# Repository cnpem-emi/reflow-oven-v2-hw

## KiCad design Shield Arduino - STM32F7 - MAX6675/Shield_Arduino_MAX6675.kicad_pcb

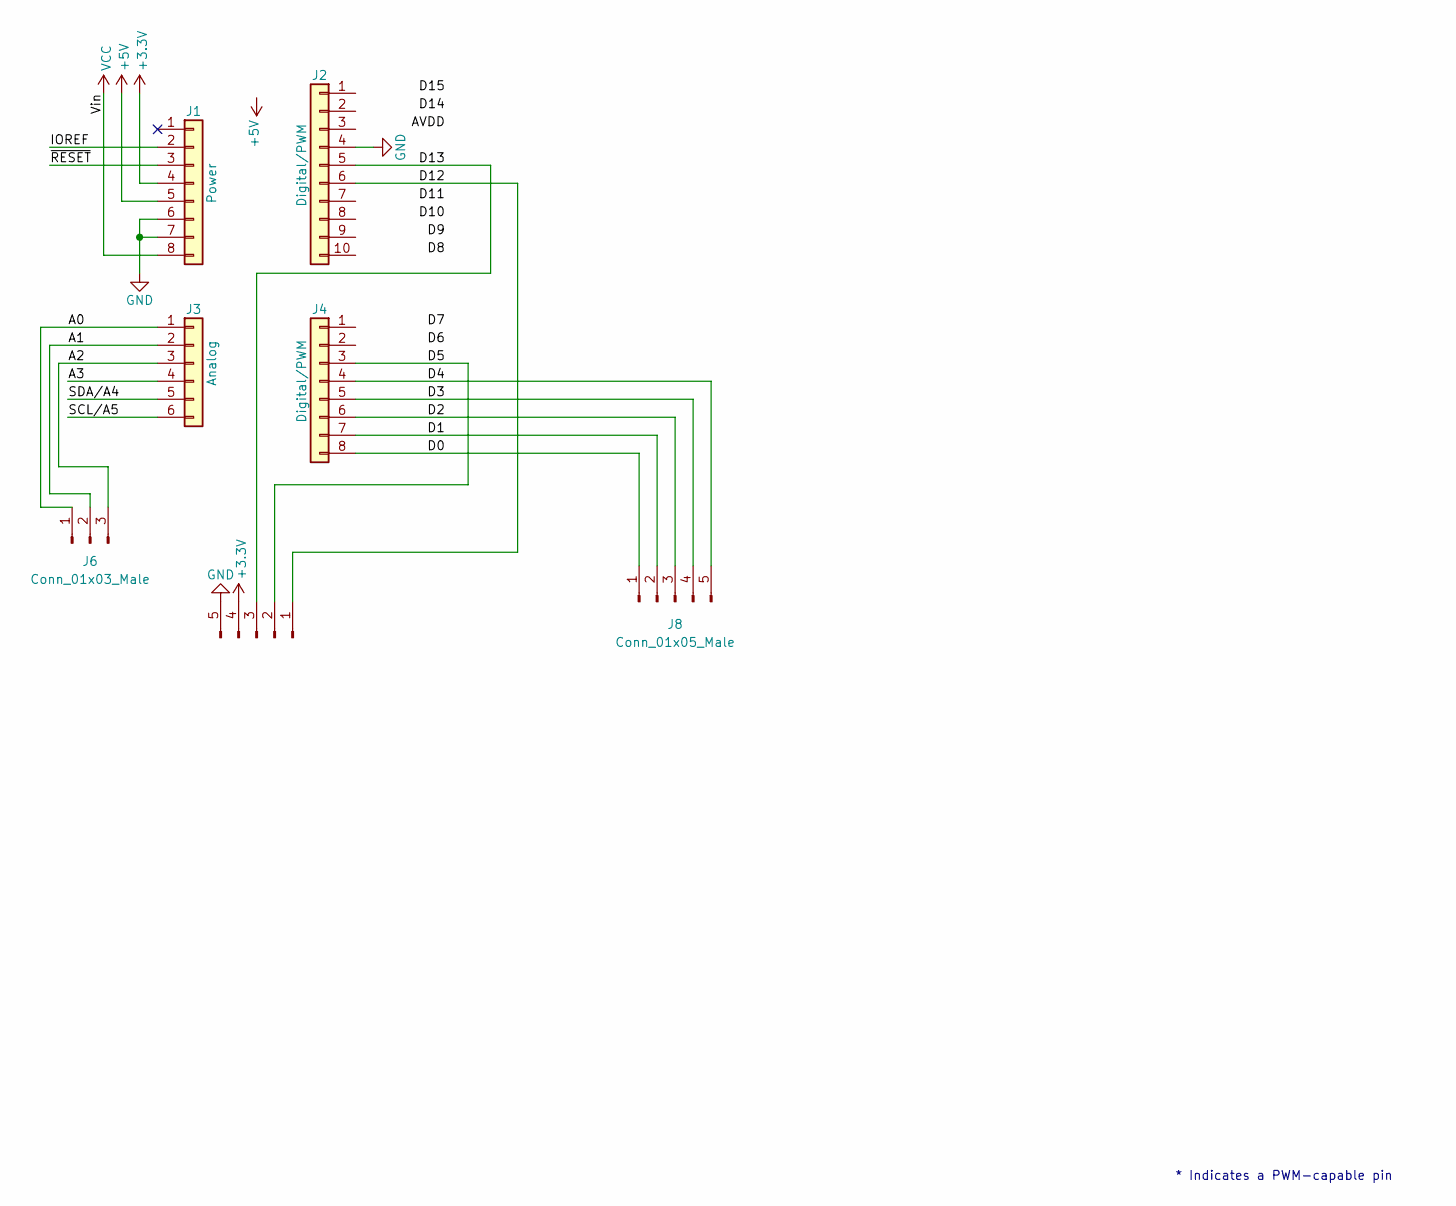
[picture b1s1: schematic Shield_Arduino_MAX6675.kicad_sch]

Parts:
J1: Power; PinSocket_1x08_P2.54mm_Vertical
J2: Digital/PWM; PinSocket_1x10_P2.54mm_Vertical
J3: Analog; PinSocket_1x06_P2.54mm_Vertical
J4: Digital/PWM; PinSocket_1x08_P2.54mm_Vertical
J5, J8: Conn_01x05_Male; PinHeader_1x05_P2.54mm_Horizontal
J6: Conn_01x03_Male; PinHeader_1x03_P2.54mm_Horizontal

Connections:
+3V3: J1.4, J5.4
+5V: J1.5
/A0: J3.1, J6.1
/A1: J3.2, J6.2
/A2: J3.3, J6.3
/A3: J3.4
/D0: J4.8, J8.1
/D1: J4.7, J8.2
/D2: J4.6, J8.3
/D3: J4.5, J8.4
/D4: J4.4, J8.5
/D5: J4.3, J5.2
/D12: J2.6, J5.1
/D13: J2.5, J5.3
/IOREF: J1.2
/SCL/A5: J3.6
/SDA/A4: J3.5
/~RESET: J1.3
GND: J1.6, J1.7, J2.4, J5.5
VCC: J1.8

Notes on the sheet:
* Indicates a PWM-capable pin

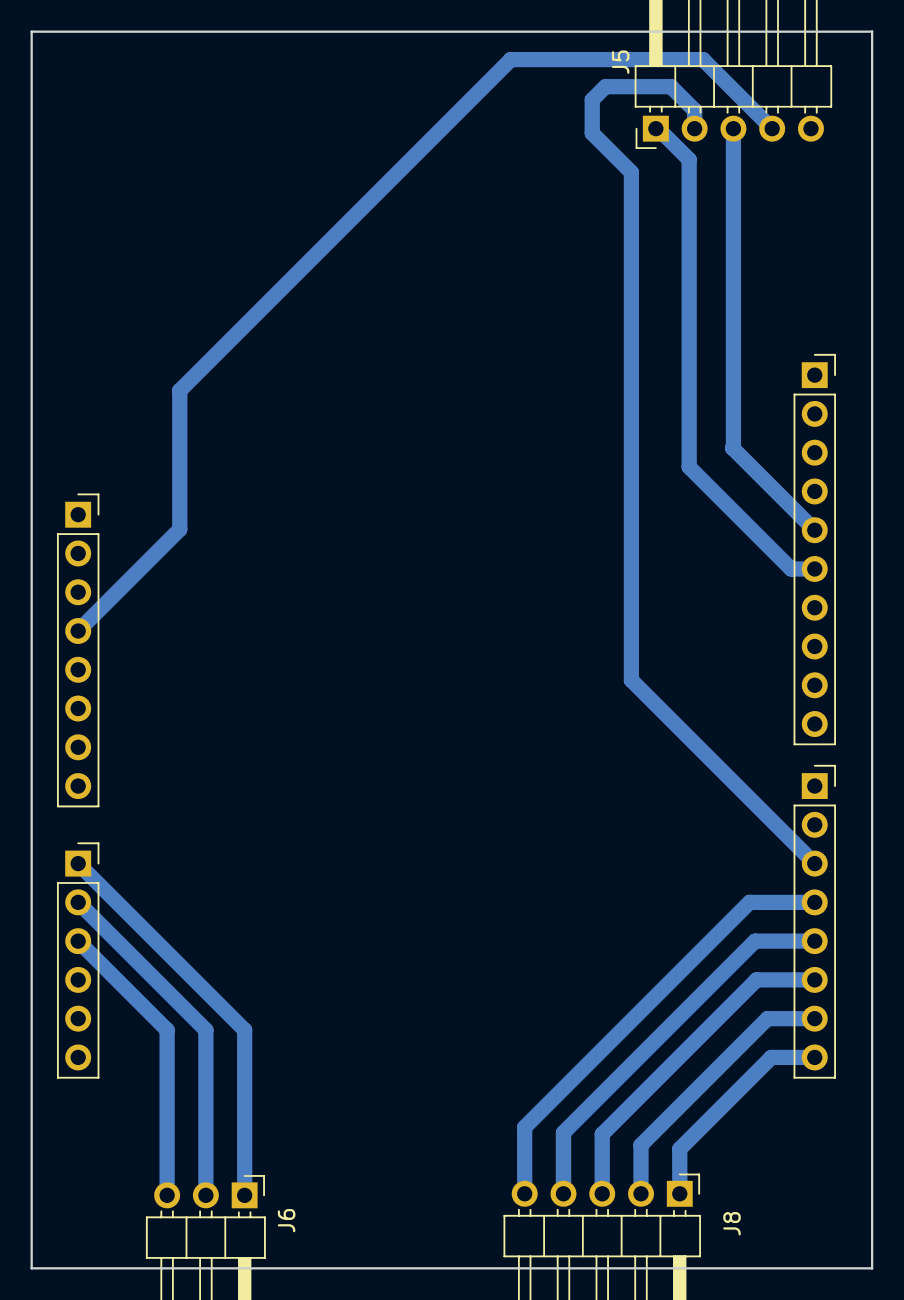
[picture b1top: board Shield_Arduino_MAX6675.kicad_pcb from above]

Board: 2 copper layers, 55.1 x 81.0 mm, 7 parts (0 on the bottom side), 13 nets.

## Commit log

2023-11-09 Arduino shield pcb for STM32f746
2023-11-09 to place old paste insider the pcb folder
